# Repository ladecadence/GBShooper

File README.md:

# GBShooper

Open source hardware GameBoy™ FlashCart Reader/Programmer

This flashcart programmer, uses the firmware at (https://github.com/ladecadence/GBShooper-Firmware)

For building it, you'll need an Atmega8515L-16AI (TQFP, -8AI also ok), a ft232rl (soic28), a 6MHz xtal, and some passives, like capacitors, resistors and LEDs.

Full Bill of Materials in the BOM file (LibreOffice and PDF).

You'll also need a micro-usb "B" connector, and a GameBoy Cartridge connector. This version uses SMD replacement connectors for the Nintendo DS, you can find them online in Aliexpress or the like.

You can use this programmer to dump original cartridges, and flash DIY flashcarts and some other flashcarts based on DIY designs and nintendo mappers (or clones).
PC-Side software is being developed right now and will also be published at ladecadence.net github.

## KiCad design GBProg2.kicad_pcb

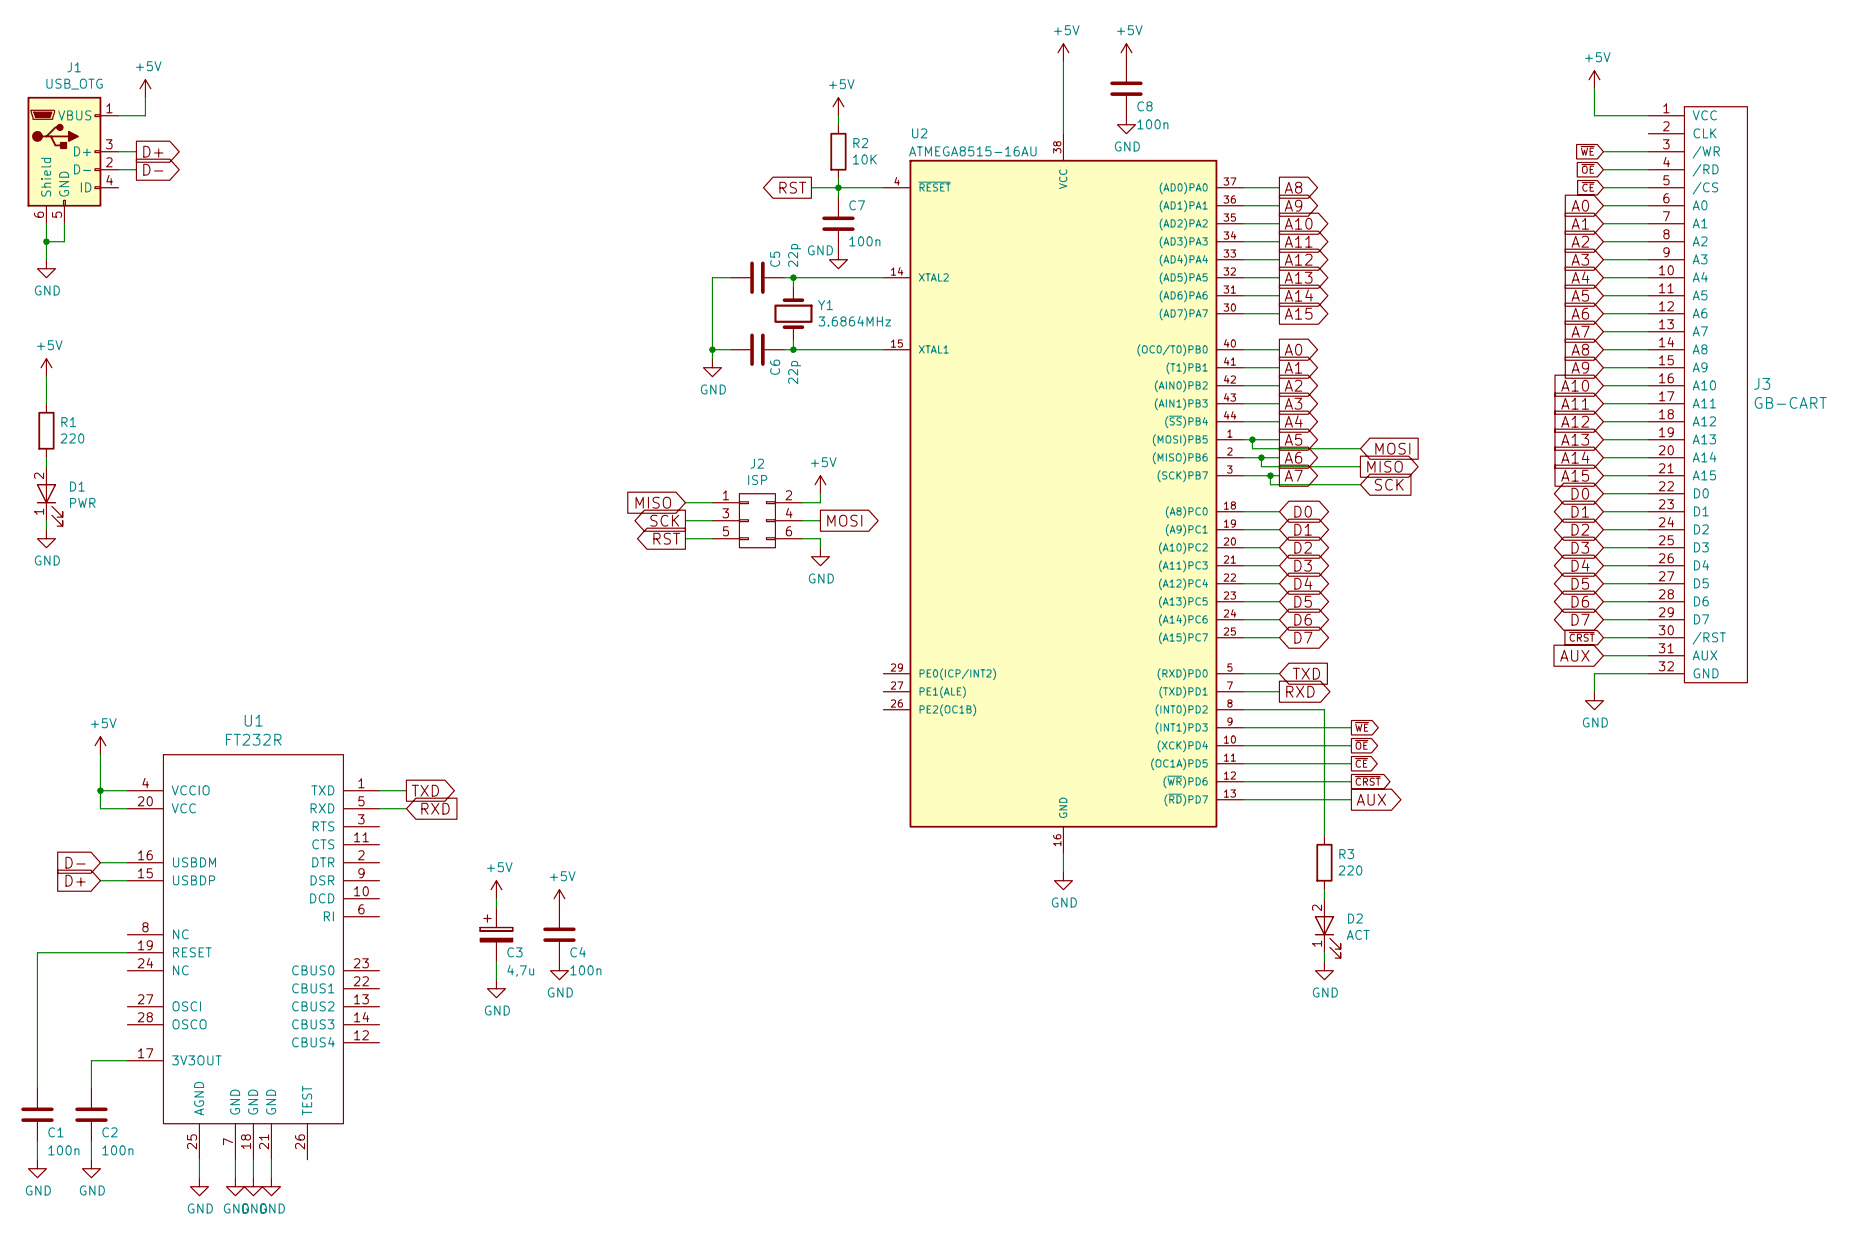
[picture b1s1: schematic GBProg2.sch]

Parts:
C1, C2, C4, C7, C8: 100n; C_0805
C3: 4,7u; CP_Elec_4x5.3
C5, C6: 22p; C_0805
D1: PWR; LED_0805
D2: ACT; LED_0805
J1: USB_OTG; USB_Micro-B
J2: ISP; Pin_Header_Straight_2x03_Pitch2.54mm
J3: GB-CART; GB-Cart-NDS-Aliexpress
R1, R3: 220; R_0805
R2: 10K; R_0805
U1: FT232R; SSOP-28_5.3x10.2mm_Pitch0.65mm
U2: ATMEGA8515-16AU; TQFP-44_10x10mm_Pitch0.8mm
Y1: 3.6864MHz; Crystal_HC49-4H_Vertical

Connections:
+5V: C3.1, C4.1, C8.1, J1.1 (VBUS), J2.2, J3.1 (VCC), R1.1, R2.1, U1.4 (VCCIO), U1.20 (VCC), U2.38 (VCC)
A0: J3.6 (A0), U2.40 ((OC0/T0)PB0)
A1: J3.7 (A1), U2.41 ((T1)PB1)
A2: J3.8 (A2), U2.42 ((AIN0)PB2)
A3: J3.9 (A3), U2.43 ((AIN1)PB3)
A4: J3.10 (A4), U2.44 ((~SS~)PB4)
A5: J2.4, J3.11 (A5), U2.1 ((MOSI)PB5)
A6: J2.1, J3.12 (A6), U2.2 ((MISO)PB6)
A7: J2.3, J3.13 (A7), U2.3 ((SCK)PB7)
A8: J3.14 (A8), U2.37 ((AD0)PA0)
A9: J3.15 (A9), U2.36 ((AD1)PA1)
A10: J3.16 (A10), U2.35 ((AD2)PA2)
A11: J3.17 (A11), U2.34 ((AD3)PA3)
A12: J3.18 (A12), U2.33 ((AD4)PA4)
A13: J3.19 (A13), U2.32 ((AD5)PA5)
A14: J3.20 (A14), U2.31 ((AD6)PA6)
A15: J3.21 (A15), U2.30 ((AD7)PA7)
AUX: J3.31 (AUX), U2.13 ((~RD~)PD7)
D0: J3.22 (D0), U2.18 ((A8)PC0)
D1: J3.23 (D1), U2.19 ((A9)PC1)
D2: J3.24 (D2), U2.20 ((A10)PC2)
D3: J3.25 (D3), U2.21 ((A11)PC3)
D4: J3.26 (D4), U2.22 ((A12)PC4)
D5: J3.27 (D5), U2.23 ((A13)PC5)
D6: J3.28 (D6), U2.24 ((A14)PC6)
D7: J3.29 (D7), U2.25 ((A15)PC7)
D+: J1.3 (D+), U1.15 (USBDP)
D-: J1.2 (D-), U1.16 (USBDM)
GND: C1.2, C2.2, C3.2, C4.2, C5.1, C6.1, C7.2, C8.2, D1.1 (K), D2.1 (K), J1.5 (GND), J1.6 (Shield), J2.6, J3.32 (GND), U1.7 (GND), U1.18 (GND), U1.21 (GND), U1.25 (AGND), U2.16 (GND)
unnamed: C1.1, U1.19 (RESET)
unnamed: C2.1, U1.17 (3V3OUT)
unnamed: C5.2, U2.14 (XTAL2), Y1.1
unnamed: C6.2, U2.15 (XTAL1), Y1.2
unnamed: D1.2 (A), R1.2
unnamed: D2.2 (A), R3.2
unnamed: R3.1, U2.8 ((INT0)PD2)
RST: C7.1, J2.5, R2.2, U2.4 (~RESET)
RXD: U1.5 (RXD), U2.7 ((TXD)PD1)
TXD: U1.1 (TXD), U2.5 ((RXD)PD0)
~CE: J3.5 (/CS), U2.11 ((OC1A)PD5)
~CRST: J3.30 (/RST), U2.12 ((~WR~)PD6)
~OE: J3.4 (/RD), U2.10 ((XCK)PD4)
~WE: J3.3 (/WR), U2.9 ((INT1)PD3)

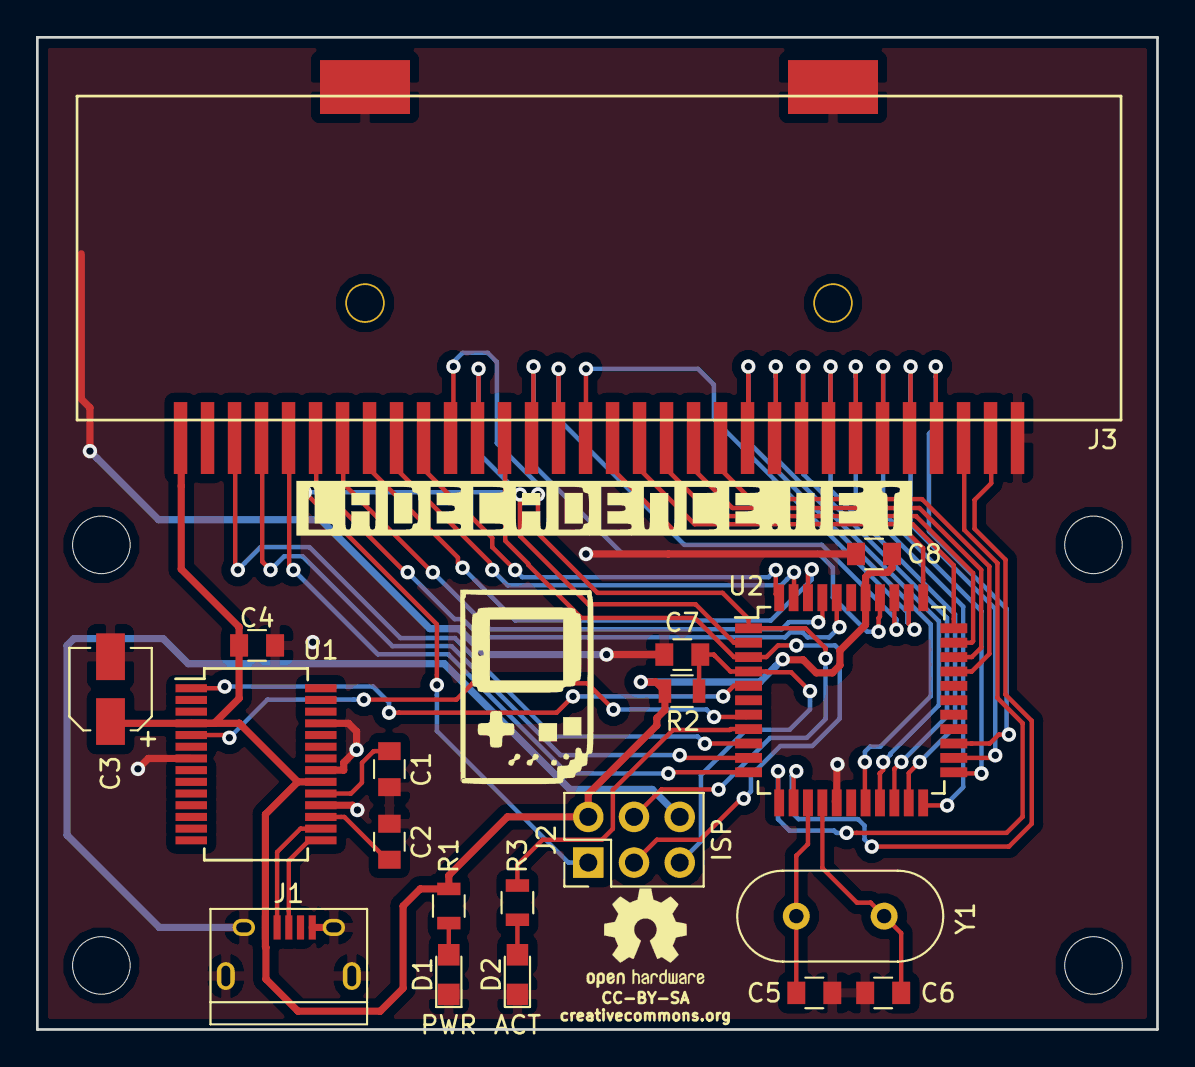
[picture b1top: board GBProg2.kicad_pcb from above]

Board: 2 copper layers, 62.2 x 55.1 mm, 19 parts (0 on the bottom side), 43 nets.

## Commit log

2019-04-10 Initial import
2019-04-10 Added license text
2019-04-10 Added license text CC-BY-SA

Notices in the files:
GBProg2.kicad_pcb:
Licensed under a Creative Commons Attribution Share-Alike License
creativecommons.org
